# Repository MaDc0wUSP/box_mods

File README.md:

An archive of projects for building various box mods.

See the README.md files in each project for more information.

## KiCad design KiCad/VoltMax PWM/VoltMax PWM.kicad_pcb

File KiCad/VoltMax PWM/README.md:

# VoltMax PWM v1 

MIC1557 PWM with reverse polarity protection.

Base schematics and concept by Mark Mathis @ Voltrove Electronics - http://voltrove.com

Additional Digipot, regulator schematics, original PCB base design, and lots of optimization by David Gabel @ MosMax Electronics - http://MosMax.com

Designed by MaDc0w

Notes:

- Supports 2-3S

- Will fire @ 100% in a reverse polarity condition. It won't auto fire though, as the timer is only powered when you hit the switch.

Board-A: 
- Alpinetech DNA75C/DNA250C compatible enclosure with or without 12mm momentary switch cutout.

Board-B: 
- ModMaker/StealthVape DNA75C/DNA250C compatible enclosure with or without 12mm momentary switch cutout.

Components:

* C1
    * https://www.mouser.com/ProductDetail/710-885012206050
    * https://www.digikey.com/product-detail/en/wurth-electronics-inc/885012206050/732-7969-1-ND

* C2 
    * https://www.mouser.com/ProductDetail/581-060316C104K
    * https://www.digikey.com/product-detail/en/avx-corporation/0603YC104KAT2A/478-1239-1-ND

* C3 
    * https://www.mouser.com/ProductDetail/81-GRM188R61C106KALJ
    * https://www.digikey.com/product-detail/en/murata-electronics-north-america/GRM188R61C106KAALJ/490-12736-1-ND

* C4 
    * https://www.mouser.com/ProductDetail/81-GRM188R61C106KALJ
    * https://www.digikey.com/product-detail/en/murata-electronics-north-america/GRM188R61C106KAALJ/490-12736-1-ND

* D1 
    * https://www.mouser.com/ProductDetail/667-DB4X313K0R
    * https://www.digikey.com/product-detail/en/panasonic-electronic-components/DB4X313K0R/DB4X313K0RCT-ND

* D2 
    * https://www.mouser.com/ProductDetail/755-RBR3LAM30ATR
    * https://www.digikey.com/product-detail/en/rohm-semiconductor/RBR3LAM30ATR/RBR3LAM30ACT-ND

* D3

   * Red LED    
       * https://www.mouser.com/ProductDetail/Lumex/SSL-LX40FT3ID
   
   * Yellow LED 
       * https://www.mouser.com/ProductDetail/696-SSL-LX40FT3YD
   
   * Green LED  
       * https://www.mouser.com/ProductDetail/696-SSL-LX40FT3GD

* D3-SPACER 
    * https://www.mouser.com/ProductDetail/749-ELM-2-1MM
    * https://www.digikey.com/product-detail/en/bivar-inc/ELM-2-1MM/ELM2-1MM-ND

* IC1 
    * https://www.mouser.com/ProductDetail/700-DS1809Z-010
    * https://www.digikey.com/product-detail/en/maxim-integrated/DS1809Z-010/DS1809Z-010-ND

* IC2 
    * https://www.mouser.com/ProductDetail/863-NCV4264-2ST50T3G
    * https://www.digikey.com/product-detail/en/on-semiconductor/NCV4264-2ST50T3G/NCV4264-2ST50T3GOSCT-ND

* Q1 
    * https://www.mouser.com/ProductDetail/757-SSM3J334RLF
    * https://www.digikey.com/product-detail/en/toshiba-semiconductor-and-storage/SSM3J334RLF/SSM3J334RLFCT-ND

* Q2 
    * https://www.mouser.com/ProductDetail/771-PSMN1R2-25YL%2c115
    * https://www.digikey.com/product-detail/en/nexperia-usa-inc/PSMN1R2-25YL115/1727-4277-1-ND

* R1 
    * https://www.mouser.com/ProductDetail/755-KTR03EZPJ105
    * https://www.digikey.com/product-detail/en/rohm-semiconductor/KTR03EZPJ105/RHM1.0MAZCT-ND

* R2 
    * https://www.mouser.com/ProductDetail/RCS060310K0FKEA
    * https://www.digikey.com/product-detail/en/vishay-dale/RCS060310K0FKEA/541-2795-1-ND

* R3 
    * https://www.mouser.com/ProductDetail/CRCW06031K00FKEAHP
    * https://www.digikey.com/product-detail/en/vishay-dale/CRCW06031K00FKEAHP/541-1.00KSCT-ND

* R4 
    * https://www.mouser.com/ProductDetail/CRCW0805560RFKEAHP
    * https://www.digikey.com/product-detail/en/vishay-dale/CRCW0805560RFKEAHP/541-560TCT-ND

* S1, S2, S3 
    * https://www.mouser.com/ProductDetail/653-B3SL-1005P
    * https://www.digikey.com/product-detail/en/omron-electronics-inc-emc-div/B3SL-1005P/SW1203CT-ND

* S4 
    * https://www.mouser.com/ProductDetail/CK/SS12D07VG4NSGAPA
    * https://www.digikey.com/product-detail/en/c-k/SS-12D07-VG-4-NS-GA-PA/CKN10397-ND

* U1 
    * https://www.mouser.com/ProductDetail/998-MIC1557YM5TR
    * https://www.digikey.com/product-detail/en/microchip-technology/MIC1557YM5-TR/576-1055-1-ND

Pad wiring:

510- to 510 negative

BAT- to battery negative

VIN+ to battery positive

F1 & F2 to 12mm momentary switch (if used)

VM+ to voltmeter positive wire (red)

VM- to voltmeter negative wire (black)

Other wiring:

Voltmeter measurement wire (white or yellow) to 510+

510+ to battery positive

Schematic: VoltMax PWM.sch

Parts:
C1: 0.47uF; C_0603_1608Metric
C2: 100nF; C_0603_1608Metric
C3, C4: 10uF; C_0603_1608Metric
D1: DB4X313K0R; Manufacturer_Part_Number DB4X313K0R; Mouser Part Number 667-DB4X313K0R
D2: RBR3LAM30A; RBR5LAM60ATR
D3: LED; LED_4mm
IC1: DS1809Z-010+; Manufacturer_Part_Number DS1809Z-010+; Mouser Part Number 700-DS1809Z-010
IC2: NCV4264-2ST50T3G; Manufacturer_Part_Number NCV4264-2ST50T3G; Mouser Part Number 863-NCV4264-2ST50T3G
J1: BAT-; SolderWirePad_single_2-75mmDrill
J2: 510-; SolderWirePad_single_2-75mmDrill
J3: VIN+; PAD_22G
J4: PAD_Fire2; PAD_22G
J5: PAD_Fire1; PAD_22G
J6: VM-; PAD_22G
J7: VM+; PAD_22G
Q1: SSM3J334R_LF; Manufacturer_Part_Number SSM3J334R,LF(T
Q2: PSMN1R2-25YLC_115; Manufacturer_Part_Number PSMN1R2-25YLC,115; Mouser Part Number 771-PSMN1R225YLC115
R1: 1M; R_0603_1608Metric
R2: 10K; R_0603_1608Metric
R3: 1K; R_0603_1608Metric
R4: 570; R_0603_1608Metric
S1, S2, S3: KSC641JLFS; Manufacturer_Part_Number KSC641JLFS
S4: SS12D07VG4NSGAPA; SS-12D07-VG4NSGAPA; Manufacturer_Part_Number SS12D07VG4NSGAPA; Mouser Part Number 611-SS12D07VG4NSGAPA
U1: MIC1557YM5_TR; Manufacturer_Part_Number MIC1557YM5 TR; Mouser Part Number N/A

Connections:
/510-: J2.1, Q2.5, Q2.6
/CStoR2: J4.1, R2.1, S1.3, S1.4, U1.3
/D2toSTR: C4.1, D2.1 (K), IC1.3
/Down: IC1.7, S3.3, S3.4
/POT0%: D1.1, IC1.4
/POT100%: D1.3, IC1.1
/R5toD3: D3.2 (A), R4.1
/S1toVS: C3.1, D2.2 (A), IC1.8, IC2.3, J5.1, S1.1, S1.2, U1.4
/U1OUT: IC1.6, R3.1, U1.5
/UP: IC1.2, S2.3, S2.4
/VIN+fromQ1Source: C2.1, IC2.1, J7.1, Q1.2
/VIN+toR5: Q1.3, R4.2, S4.2
/VIN+toSwitch: J3.1, S4.1
GND: C1.2, C2.2, C3.2, C4.2, D3.1 (K), IC1.5, IC2.2, IC2.4, J1.1, J6.1, Q1.1, Q2.1, Q2.2, Q2.3, R1.2, R2.2, S2.1, S2.2, S3.1, S3.2, U1.2
unnamed: C1.1, D1.2, D1.4, U1.1
unnamed: Q2.4, R1.1, R3.2

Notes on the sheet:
VMM to 510+
VIN+ PAD to BATT+
510- PAD to 510-
BATT- PAD to BATT-

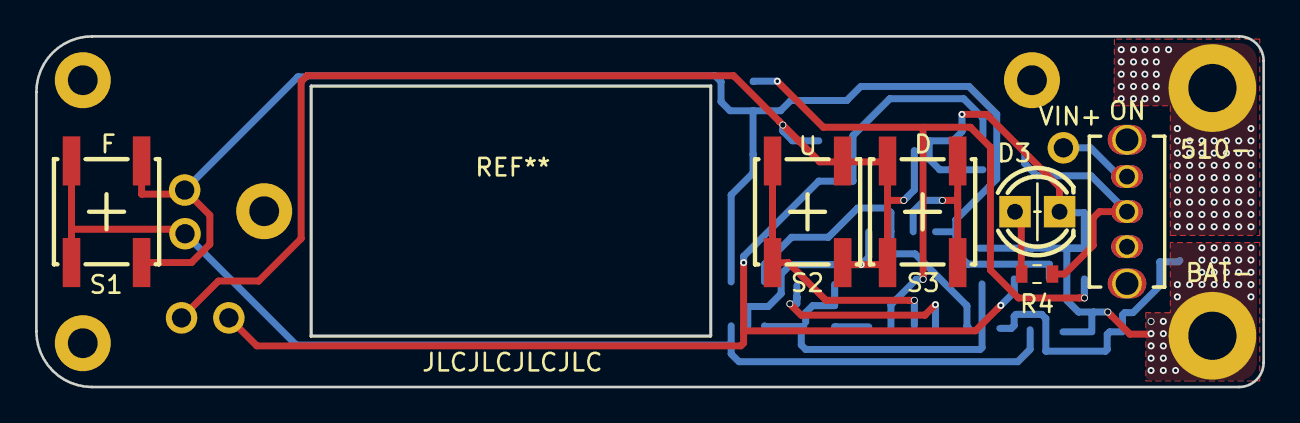
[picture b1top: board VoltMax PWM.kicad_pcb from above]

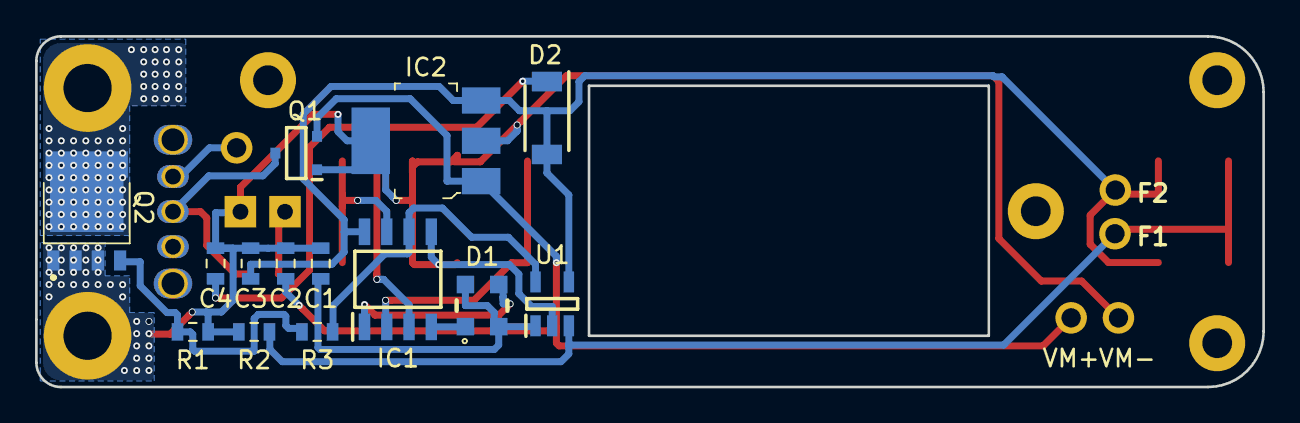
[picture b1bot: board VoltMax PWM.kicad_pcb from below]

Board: 2 copper layers, 70.0 x 20.0 mm, 31 parts (14 on the bottom side), 16 nets.

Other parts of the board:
PAD1, PAD2, PAD3, PAD4_VM: Mount_PAD_VM

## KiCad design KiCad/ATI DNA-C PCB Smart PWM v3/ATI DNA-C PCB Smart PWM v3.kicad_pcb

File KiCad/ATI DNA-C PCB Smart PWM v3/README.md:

# SPWM V3 

Brought to you by David Gabel - http://MosMax.com

KiCad rewrite by MaDc0w

Alpinetech DNA75C/DNA250C enclosure with or without 12mm momentary switch cutout style board for the Smart PWM V3 which can be attached with 2.54mm pitch header pins. 0.36" 3-wire voltmeter in cutout.

Components:

D1 - [red](https://www.mouser.com/ProductDetail/Lumex/SSL-LX40FT3ID?qs=%2fha2pyFadujxBjlUmTzxXrCIgmGlcT2WBxtU6kQaw6TtNoou84YoUQ%3d%3d), [green](https://www.mouser.com/ProductDetail/Lumex/SSL-LX40FT3GD?qs=sGAEpiMZZMtmwHDZQCdlqVsz6Sp3LtaXupd43WLqkcA%3D) or [yellow](https://www.mouser.com/ProductDetail/Lumex/SSL-LX40FT3YD?qs=sGAEpiMZZMtmwHDZQCdlqVsz6Sp3LtaXUiOcvLs1KM8%3D)

D1-SPACER - https://www.mouser.com/ProductDetail/749-ELM-2-1MM

R1 - 0805 case current limiting resistor for D1. To determine value, look at datasheet for the LED, know the max voltage of your batteries & use an LED resistor calculator

S1, S2, S3 - https://www.mouser.com/ProductDetail/Omron-Electronics/B3SL-1005P?qs=FfQ8ThoHJhGe9QOr6%252bon8g%3D%3D

S4 - https://www.mouser.com/ProductDetail/CK/SS12D07VG4NSGAPA?qs=%2fha2pyFadugjks%2fHbHkDhssP9iJkVnkua0Q3TVFHBfbSkpRFT8OjGg%3d%3d

Pad wiring:

B+ to battery positive

F1 & F2 to 12mm momentary switch

VMM to voltmeter measurement wire (white or yellow)

VM+ to voltmeter positive wire (red)

VM- to voltmeter negative wire (black)

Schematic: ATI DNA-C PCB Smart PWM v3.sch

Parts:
D1: LED; LED_4mm
PAD_Fire1: Conn_01x01; PAD_22G
PAD_Fire_GND1: Conn_01x01; PAD_22G
R1: R; R_0805_2012
S1, S2, S3: KSC641JLFS; Manufacturer_Part_Number KSC641JLFS; Mouser Part Number 653-B3SE-1002P
S4: SS-12D07-VG4NSGAPA; Manufacturer_Part_Number SS12D07VG4NSGAPA; Mouser Part Number 611-SS12D07VG4NSGAPA
U1: SmartPWMv3; SmartPWM_V3
VM+1: Conn_01x01; PAD_24G
VMM1: Conn_01x01; PAD_24G
VM_GND1: Conn_01x01; PAD_24G

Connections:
+BATT: S4.1; also elsewhere on the board
/Down: S3.3, S3.4, U1.3
/Fire: PAD_Fire1.1, S1.3, S1.4, U1.8
/GND: D1.1 (K), PAD_Fire_GND1.1, S1.1, S1.2, S2.1, S2.2, S3.1, S3.2, U1.10, VM_GND1.1
/LED+: D1.2 (A), R1.2
/POT: U1.4
/Up: S2.3, S2.4, U1.2
/VIN: R1.1, S4.2, U1.1
/VM+: U1.6, VM+1.1
/VMM: U1.5, VMM1.1

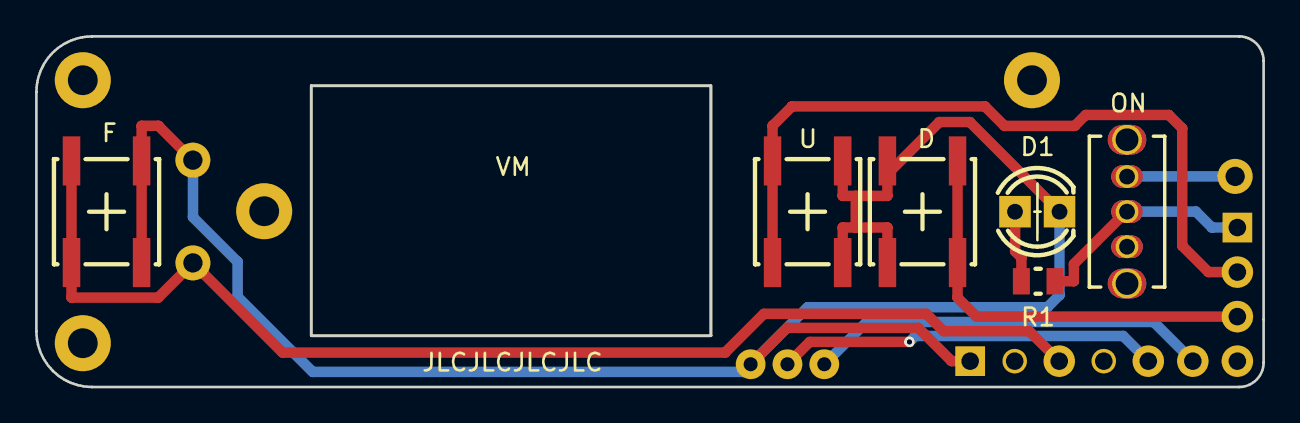
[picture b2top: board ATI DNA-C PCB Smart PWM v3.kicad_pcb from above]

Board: 2 copper layers, 70.0 x 20.0 mm, 18 parts (0 on the bottom side), 9 nets.

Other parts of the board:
PAD1, PAD2, PAD3, PAD4_VM: Mount_PAD
PAD_22G: BAT1; PAD_22G
VM: 0.36_inch_VM

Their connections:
+BATT: PAD_22G.1; also elsewhere on the board

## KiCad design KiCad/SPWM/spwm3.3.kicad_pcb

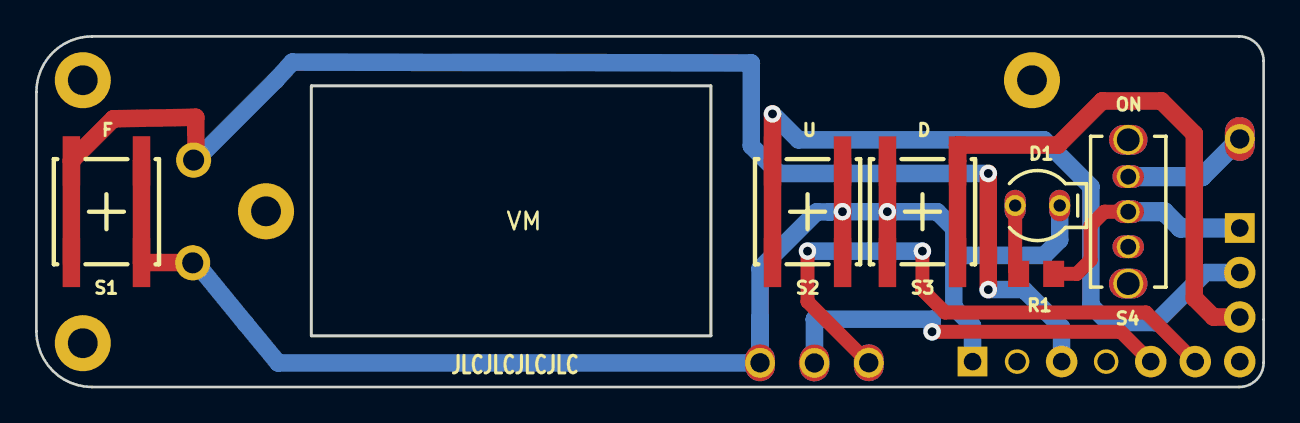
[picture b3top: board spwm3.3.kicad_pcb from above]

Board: 2 copper layers, 70.0 x 20.0 mm, 18 parts (0 on the bottom side), 9 nets.

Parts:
D1: LED ON; SSL-LX40FT3ID
Pad1, Pad3, Pad5, Pad6: PAD; Pad
Pad4: PAD; Pad_Pad4
Pad7: PAD; Pad_Pad7
R1: RES D1 CURRENT LIMIT; RES_0805edit
S1: Fire; KSC641JLFS
S2: Up; KSC641JLFS
S3: Down; KSC641JLFS
S4: Off-On; SS-12D07-VG4NSGAPA
U1: SMARTPWM V3; SmartPWM_V3
U4: 24G PAD; 24g_pad_U4
U5, U6, U7: 24G PAD; 24g_pad_U5
VM: VM

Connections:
BAT+: S4.1, U4.1
DOWN: S3.3, S3.4, U1.10
FIRE_SW: Pad4.1, S1.3, S1.4, U1.5
GND: D1.1, Pad7.1, S1.1, S1.2, S2.1, S2.2, S3.1, S3.2, U1.3, U7.1
LED+: D1.2, R1.1
UP: S2.3, S2.4, U1.11
VIN: R1.2, S4.2, U1.12
VM+: U1.7, U5.1
VM_Meaure: U1.8, U6.1

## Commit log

2019-03-06 New daughterboard for Smart PWM V3(Rev C)
2019-03-06 Update silkscreen, Generate new Gerbers
2019-03-06 Update main README
2019-03-09 Update all the things
2019-03-09 Cleanup
2019-03-11 Cleanup and make pretty rendering
2019-03-18 Cleanup SPWM, Upload from scratch written project with proper schematic
2019-03-18 Make pretty
2019-03-24 Wrong license
2019-03-24 Add correct license
2019-03-25 Change/Cleanup 3D models - Add silkscreen gfx
2019-03-25 Derp
2019-03-25 More Derp - Fixed
2019-03-25 Requested change
2019-03-26 Beef up pads, add MorningMist logo
2019-03-26 New Gerbers
2019-04-04 v2 cleanup
2019-04-05 v3 suggestions from David
2019-04-07 Improve thermal, add 3D models, rename project
2019-04-07 Small fixes
2019-04-08 Better thermal, cleaner vias/traces
2019-04-14 David has spoken and changes have been made, cleaner vias/traces
2019-04-14 Silkmask and cleanup
2019-04-15 Update schematic
2019-04-15 Create README, Add BOM
2019-04-15 Stupid markup..
2019-04-15 Newer Pics
2019-04-16 Fix resistor package sizes
2019-04-16 Add alternative links for components
2019-04-16 Rename Boards,Add ModMaker/StealthVape box layout
2019-04-19 Resize some wire pads
